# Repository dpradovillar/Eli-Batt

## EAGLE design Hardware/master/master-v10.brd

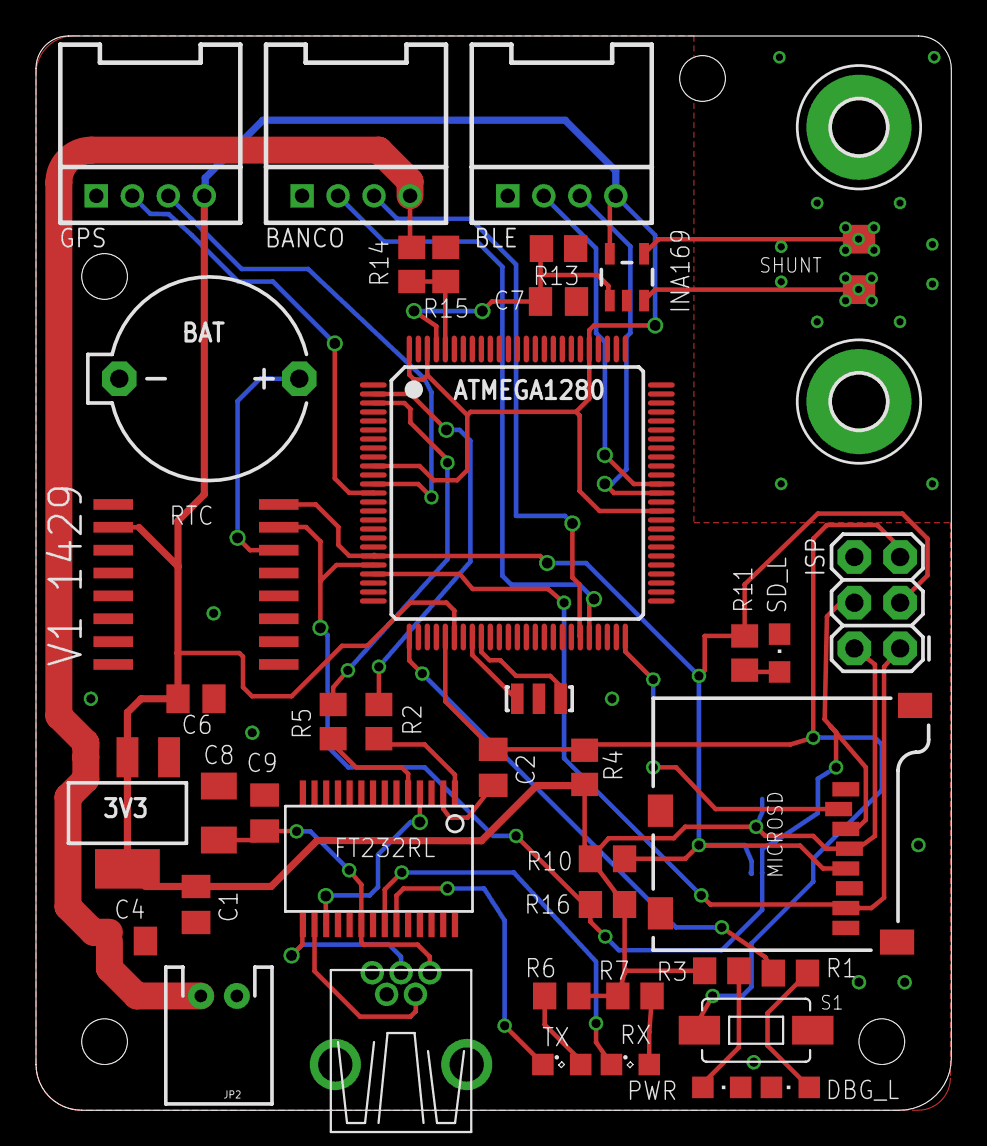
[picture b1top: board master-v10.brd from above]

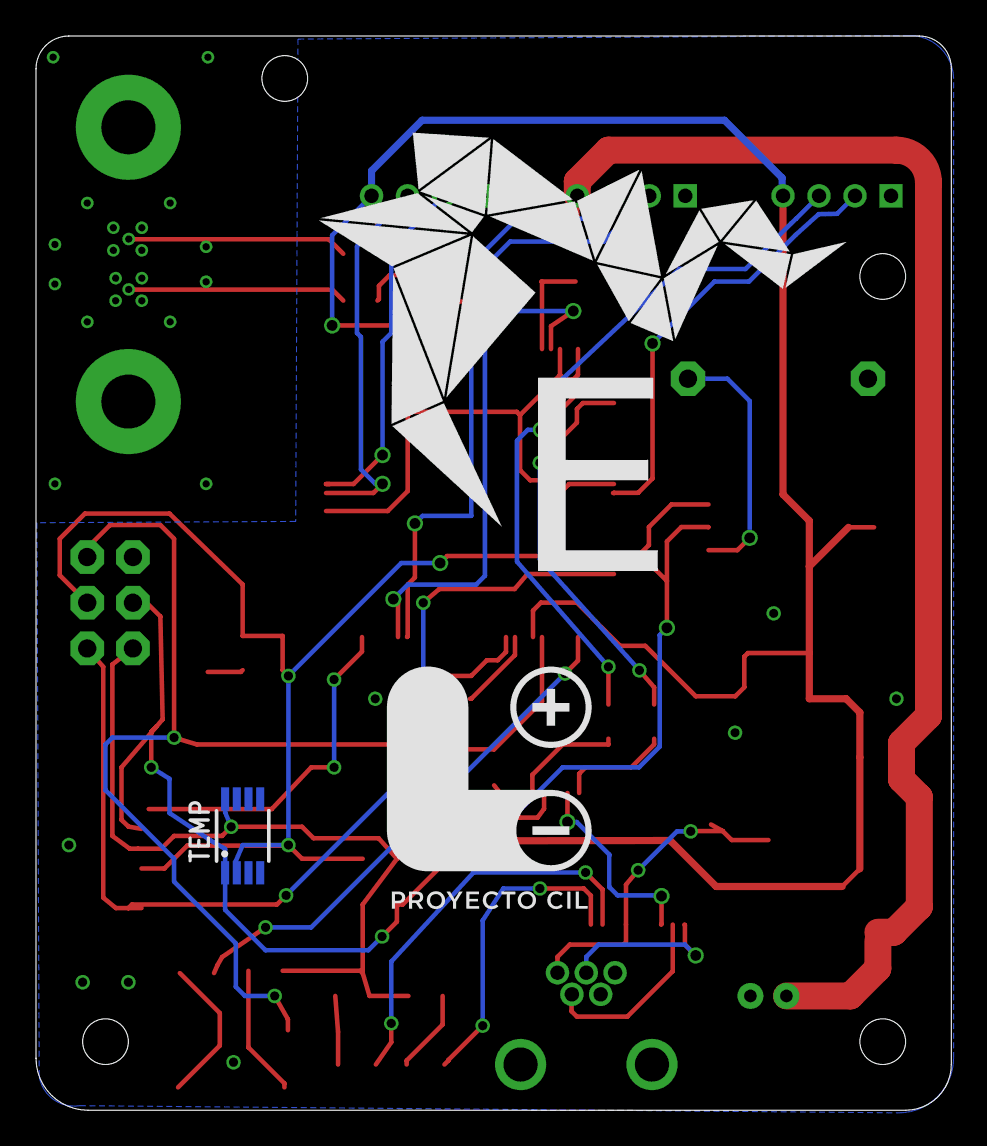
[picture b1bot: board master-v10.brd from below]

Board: 2 copper layers, 50.9 x 59.7 mm, 47 parts (4 on the bottom side), 38 nets.

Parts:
3V3: AP1117E; SOT223
ATMEGA1280: ATMEGA640/1280/2560-A; TQFP100A
BANCO: TWIG-2.0-DIPD; 2.0_1X4_90
BAT: CR1220
BLE: TWIG-2.0-DIPD; 2.0_1X4_90
C1, C4: 10uF; C0805K
C2, C6, C7, C9: 0.1uF; C0805K
C8: 10uF; C1206K
DBG_L: CHIPLED_0805
FRAME1: FRAME-LEDGER; CREATIVE_COMMONS
FT232RL: FT232RL-BASICSSOP; SSOP28DB
GPS: TWIG-2.0-DIPD; 2.0_1X4_90
INA169: INA169; SOT23-5
ISP: AVR_SPI_PRG_6PTH; 2X3
JP1: USB-MB-H
JP2: M02JST-PTH-2; JST-2-PTH
MICROSD: USD-SOCKETNEW; MICRO-SD-SOCKET-PP
OSC: RESONATOR-SMD
PWR: RED; CHIPLED_0805
R1, R3: 1K; R0805
R2, R5, R11: 1k; R0805
R4: 10K; R0805
R6, R7: 10; R0805
R10, R14, R16: 10k; R0805
R13: 82k; R0805
R15: 3.3k; R0805
RTC: DS3231/SO; SO16W
RX: Green; SML0805
S1: SWITCH-MOMENTARY-2-SMD-1101NE; TACTILE-SWITCH-1101NE
SD_L: CHIPLED_0805
SHUNT: 0.002; 1206
TEMP: MCP9804; MSOP8
TX: Red; SML0805
U$1: LOGO_CIL
U$2: LOGO_ELIBATT
V_IN: MOUNT-PAD-ROUND3.0; 3,0-PAD
V_OUT: MOUNT-PAD-ROUND3.0; 3,0-PAD

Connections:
3.3V: 3V3.2, 3V3.4, ATMEGA1280.10, ATMEGA1280.31, ATMEGA1280.61, ATMEGA1280.80, ATMEGA1280.98, ATMEGA1280.100, BLE.4, C1.1, C6.1, GPS.4, INA169.5, ISP.2, MICROSD.4, R3.2, R4.2, R6.2, R7.2, R10.1, R16.1, RTC.2, TEMP.8
BT_RX: ATMEGA1280.64, BLE.2
BT_TX: ATMEGA1280.63, BLE.3
COMM_RX: ATMEGA1280.46, BANCO.2
COMM_TX: ATMEGA1280.45, BANCO.3
CS_SD: ATMEGA1280.50, MICROSD.2
DTR: C2.2, FT232RL.2
GND: 3V3.1, ATMEGA1280.11, ATMEGA1280.32, ATMEGA1280.62, ATMEGA1280.81, ATMEGA1280.99, BANCO.1, BAT.-, BLE.1, C1.2, C4.2, C6.2, C7.2, C8.2, C9.2, DBG_L.C, FT232RL.7, FT232RL.11, FT232RL.18, FT232RL.21, FT232RL.25, FT232RL.26, GPS.1, INA169.2, ISP.6, JP1.GND, JP2.1, MICROSD.6, MICROSD.GND1, MICROSD.GND3, OSC.2, PWR.C, R13.1, R15.1, RTC.5, RTC.6, RTC.7, RTC.8, RTC.9, RTC.10, RTC.11, RTC.12, RTC.13, S1.P$1, SD_L.C, TEMP.4, TEMP.5, TEMP.6, TEMP.7
MISO: ATMEGA1280.22, ISP.1, MICROSD.7
MOSI: ATMEGA1280.21, ISP.4, MICROSD.3, R16.2, RTC.15, TEMP.1
unnamed: BAT.+, RTC.14
unnamed: ATMEGA1280.34, OSC.1
unnamed: DBG_L.A, R1.2
unnamed: ATMEGA1280.26, R1.1
unnamed: FT232RL.15, JP1.D+
unnamed: FT232RL.1, R2.1
unnamed: PWR.A, R3.1
unnamed: FT232RL.5, R5.1
unnamed: FT232RL.22, RX.C
unnamed: R7.1, RX.A
unnamed: FT232RL.23, TX.C
unnamed: R6.1, TX.A
unnamed: ATMEGA1280.33, OSC.3
unnamed: FT232RL.16, JP1.D-
unnamed: R11.2, SD_L.A
unnamed: C8.1, C9.1, FT232RL.20, JP1.VBUS
unnamed: FT232RL.4, FT232RL.17
RAW: 3V3.3, BANCO.4, C4.1, JP2.2, R14.1
RST: ATMEGA1280.30, C2.1, ISP.5, R4.1, S1.P$2
RX_FT232: ATMEGA1280.3, R5.2
RX_GPS: ATMEGA1280.13, GPS.2
SCK: ATMEGA1280.20, ISP.3, MICROSD.5, R10.2, R11.1, RTC.16, TEMP.2
SENSOR_CURRENT: ATMEGA1280.97, C7.1, INA169.1, R13.2
SENSOR_VOLT: ATMEGA1280.96, R14.2, R15.2
TX_FT232: ATMEGA1280.2, R2.2
TX_GPS: ATMEGA1280.12, GPS.3
VIN+: INA169.3, SHUNT.2, V_IN.B3,0
VIN-: INA169.4, SHUNT.1, V_OUT.B3,0

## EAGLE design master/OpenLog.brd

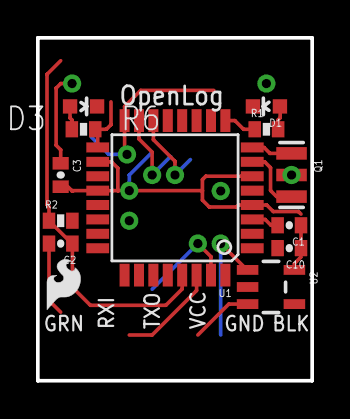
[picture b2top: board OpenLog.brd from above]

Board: 2 copper layers, 15.2 x 19.1 mm, 14 parts (0 on the bottom side), 11 nets.

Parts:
C1: 1uF; 0402-CAP
C2, C3, C10: 0.1uF; 0402-CAP
D1: Blue; LED-0603
D3: Green; LED-0603
Q1: 16MHz; RESONATOR-SMD
R1, R6: 1K; 0402-RES
R2: 10K; 0402-RES
U1: ATMEGA328; TQFP32-08
U2: 3.3V MIC5205; SOT23-5
U$1: LOGO-SFESK; SFE-LOGO-FLAME
U$2: CREATIVE_COMMONS

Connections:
3.3V: U1.4, U1.6, U1.18, U1.20
5V: C1.1, C3.2, C10.1, R2.2, U2.5
GND: C1.2, C3.1, C10.2, D1.C, D3.C, Q1.2, U1.3, U1.5, U1.21, U2.2
unnamed: Q1.1, U1.8
unnamed: Q1.3, U1.7
unnamed: D1.A, R1.2
unnamed: R1.1, U1.9
unnamed: D3.A, R6.2
RAW: U2.1, U2.3
RST: C2.1, R2.1, U1.29
SCK: R6.1, U1.17

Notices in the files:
parts and their libraries:
atmel-avr: Copyright (C) 2008, Bob Starr
SparkFun-Connectors: Licensing: Creative Commons ShareAlike 4.0 International - https://creativecommons.org/licenses/by-sa/4.0
SparkFun-Aesthetics: Released under the Creative Commons Attribution Share-Alike 4.0 License
